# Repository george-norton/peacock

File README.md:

# Peacock

Peacock is an RP2040 powered trackpad running QMK. It features an integrated Microchip MaxTouch sensor IC which is connected to a 7" capacitive sensor. I also designed some little trackpads which you can integrate into your own keyboards, see [Procyon](https://github.com/george-norton/procyon).

The [Ploopy trackpad](https://ploopy.co/trackpad/) is like a more polished Peacock, with a higher resolution sensor. It runs code build from the same QMK/ZMK branches, and is easier to buy.

## Features
- Fully PCBA, this other than switches and encoders, this board is designed to be fully factory assembled.
- Integrated RP2040 controller, no need to a separate controller.
- 7 inch 16:9 capacitive sensor.
- 5 Choc/MX switches and 2 EC11/EC12 encoders.
- A [VIK](https://github.com/sadekbaroudi/vik) connection between the controller and sensor board.

## But how does it work?
The capacitive sensing IC is wired to a grid of diamond shaped electrodes. The diamonds are connected to form rows and columns. The IC scans the matrix by
applying a small voltage to the rows in turn, and then measuring voltage on the columns. Any conductive objects nearby (like your finger) will distrupt the
electrical field and can be detected.

## Sensor capabilities
The mXT336UD-MAU002 sensor IC used in this design is in fact a touchscreen controller rather than a trackpad controller. I have chosen to use a touchscreen
controller as they tend to be designed for much larger sensor areas than touchpad controller. This sensor can:
- Detect 10 concurrent touch events.
- Can support both mutual capacitance and self capacitance measurements.
- Has integrated signal processing capabilities to reduce noise, reject large touches (grip or palms) etc..
- Can be configured as a digitizer, or an array of up to 16 buttons.
- The sensor also supports a passive stylus, although the electrodes in Peacock are larger than the recommended size, so this may not perform well.

## Software support
Currently there are experimental QMK and ZMK branches with Peacock support.

The [QMK multitouch_experiment branch](https://github.com/george-norton/qmk_firmware/tree/multitouch_experiment) exteneds the QMK digitizer feature to implement real trackpad support. On this branch, the MaxTouch driver reports 5 separate finger positions to the host and it detects gestures. You should get all the same gesture support you would expect from a modern trackpad. This branch is a large changeset which will likely take some time to get merged into QMK. There are some [pre-built QMK firmware images in my userspace](https://github.com/george-norton/qmk_userspace/releases/tag/latest).

The [ZMK Maxtouch module](https://github.com/george-norton/maxtouch-zephyr-module) builds against Petes [feat/pointers-move-scroll-ptp](https://github.com/petejohanson/zmk/tree/feat/pointers-move-scroll-ptp) ZMK branch. It is currently missing LED support, and fallback to mouse emulation (so no MacOS support).

## Sensor tuning
The sensor sensitivity may require tuning depending on the type of surface you use on your build. This can be done by adjusting the touch threshold, and
if required the transmit gain. If your sensor is not detecting touches well, reduce the touch threshold. If your sensor is jittery, or is detecting spurious touches increase the touch threshold, or if there is any ungrounded metal by the sensor, move it. Increasing the transmit gain will require a larger touch threshold, but it should enable you to use thicker overlays and it will give you more room to adjust the touch threshold.

The mouse emulation gestures are implemented in software, they rely on various parameters that can be tuned by defining macros.

If you flash the QMK debug firmware, you can use the [Maxtouch debug](https://github.com/george-norton/maxtouch-debug) tool to adjust the sensor tuning in real time and see how it works.

## BOM
To build a Peacock you will need:
- Factory assembled PCBs (from, for example JLCPCB).
- 5 Choc v1 or MX switches.
- 5 keycaps.
- 2 Encoders (ec11/ec12).
- 2 Encoder knobs.
- 1 Type-A 12P 0.5 mm pitch FFC cable (ideally around 5cm long) [aliexpress](https://www.aliexpress.com/item/1005004140412156.html).
- [A 3D printed case](case/) and its mounting fixtures.
- Some sort of nice feeling insulating surface to put over the sensor, for example sticky vinyl wrap or acrylic. Ideally this should not have any air gaps, so FDM printed surfaces should be printed with 100% infill. If the surface is too thin the trackpad will not perform well, multiple layers of vinyl may be required.
- 4 rubber bumpons.

## PCB ordering guide
Use the gerbers files in the releases, most options are not critical although a thicker PCB is probably best so it does not flex too much when you press against the sensor.
I have tested with 1.6mm thickness, lead free HASL from JLCPCB.

The sensor IC is not available from LCSC, you will need to use JLCPCB's global parts sourcing service to order chips from Digikey, the digikey part number is 150-ATMXT336UD-MAU002-ND, expect a lead time of 1-2 weeks. You may also find the flash memory and LED parts go in and out of stock, so it might also be worth preordering those. The LEDs are optional, if the are not available you can always hand solder some at a later time.

You can see the correct part orientation here, when ordering ensure that all parts are correctly rotated:

The v1.0 release has been tested and it works, but there is an issue with the I2C pin allocation. As a result it requires two additional bodge wires, and the encoder switches will not work.

The v1.01 release has the issue fixed, you should order this version.

## Assembly guide

Assembly is simple as the majority of the work is done by the manufacturer. You will need to:

- Remove the edge rails by breaking them off with a pair of pliers, then cut or break the mousebites to separate the two PCBs.

- Test your PCB. Plug it in and hopefully you will see a new mass storage device. Drag and drop a firmware (uf2) file to flash it. If sucessfull, the LEDs should light up.
- Solder 5 MX/Choc switches.
- Solder 2 EC11/EC12 encoders.

- Connect both boards together using the FFC cable, the black parts of the connector can be opened to enable you to insert the cable.

- Use a thread tapping tool to create threads in the case.
- Place the boards into the case.
- Screw it in with 8xM3 6mm screws and optionally 1xM2 6mm screw near the USB port.
- Stick your surface to the sensor area. The surface is critical to the performance of the trackpad, without a surface you will likley get no movement at all. Depending on its thickness, a single piece of vinyl will likely be insufficient for the trackpad to track well, a two or three layers will work much better. I noticed that some battery powered USB hosts require additional surface thickness to track multiple fingers well.

If you build a Peacock, please post a picture in the [show and tell](https://github.com/george-norton/peacock/discussions/categories/show-and-tell).

## Firmware

Peacock support has not yet been merged back to QMK. You can find a branch with pointing device support [here](https://github.com/george-norton/qmk_firmware/tree/peacock) or the multitouch branch [here](https://github.com/george-norton/qmk_firmware/tree/multitouch_experiment) Note, this branch currently does not work with MacOS.

## VIK support

This trackpad is a VIK device, so you should be able to discard the controller portion of the build and wire the trackpad directly to a different VIK enabled controller (such as those sold by fingerpunch and splitkb). You could also replace the controller board with one of your own design.

## VIK certification

Trackpad module

| Category                | Classification          | Response           |
| ----------------------- | ----------------------- | ------------------ |
| FPC connector           | Required                | :heavy_check_mark: |
| Breakout pins           | Recommended             | :heavy_check_mark: |
| Uses: SPI               | Optional                | :x:                |
| SPI used for SPI only   | Strongly recommended    | N/A                |
| Uses: I2C               | Optional                | :heavy_check_mark: |
| I2C used for I2C only   | Strongly Recommended    | :heavy_check_mark: |
| I2C pull ups            | Required                | 3.3k               |
| Uses: RGB               | Optional                | :x:                |
| Uses: Extra GPIO 1      | Optional                | :heavy_check_mark: |
| Uses: Extra GPIO 2      | Optional                | :x:                |
| Standard PCB Size/Mount | Strongly recommended    | :x:                |

Peacock controller

| Category                 | Classification          | Response           |
| -----------------------  | ----------------------- | ------------------ |
| FPC connector            | Required                | :heavy_check_mark: |
| Breakout pins            | Recommended             | :heavy_check_mark: |
| Supplies: SPI            | Required                | :heavy_check_mark: |
| Supplies: I2C            | Required                | :heavy_check_mark: |
| I2C on main PCB          | Discouraged             | :x:                |
| I2C pull ups             | Informative             | N/A                |
| Supplies: RGB            | Required                | :heavy_check_mark: |
| Supplies: Extra GPIO 1   | Required                | Analog/Digital     |
| Supplies: Extra GPIO 2   | Required                | Analog/Digital     |

## Schematic

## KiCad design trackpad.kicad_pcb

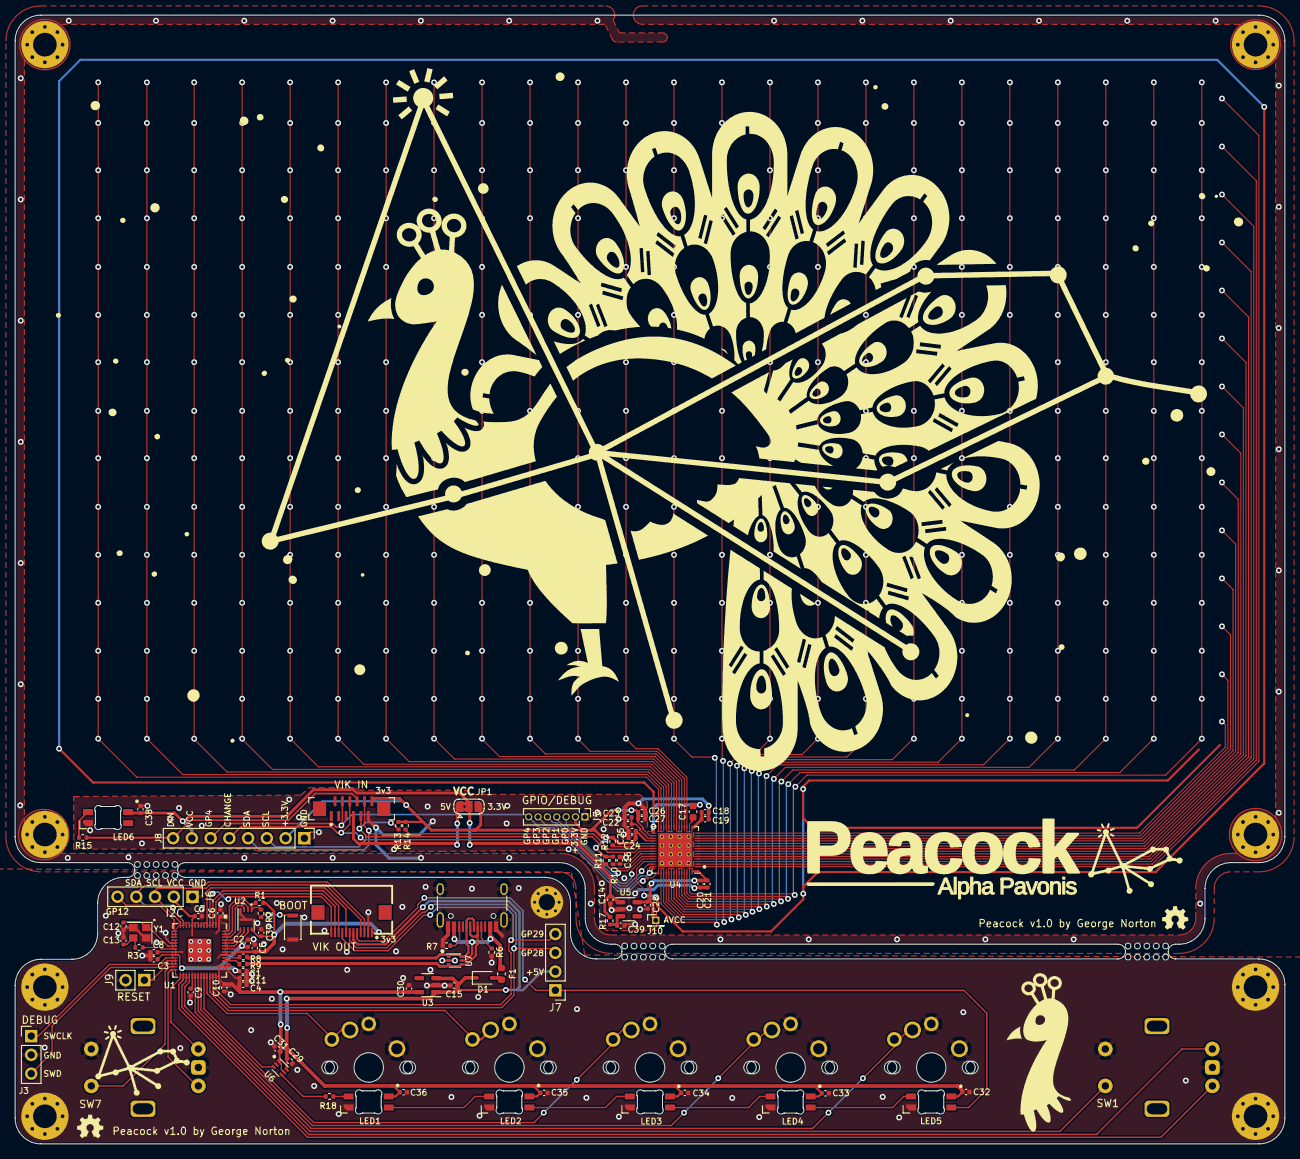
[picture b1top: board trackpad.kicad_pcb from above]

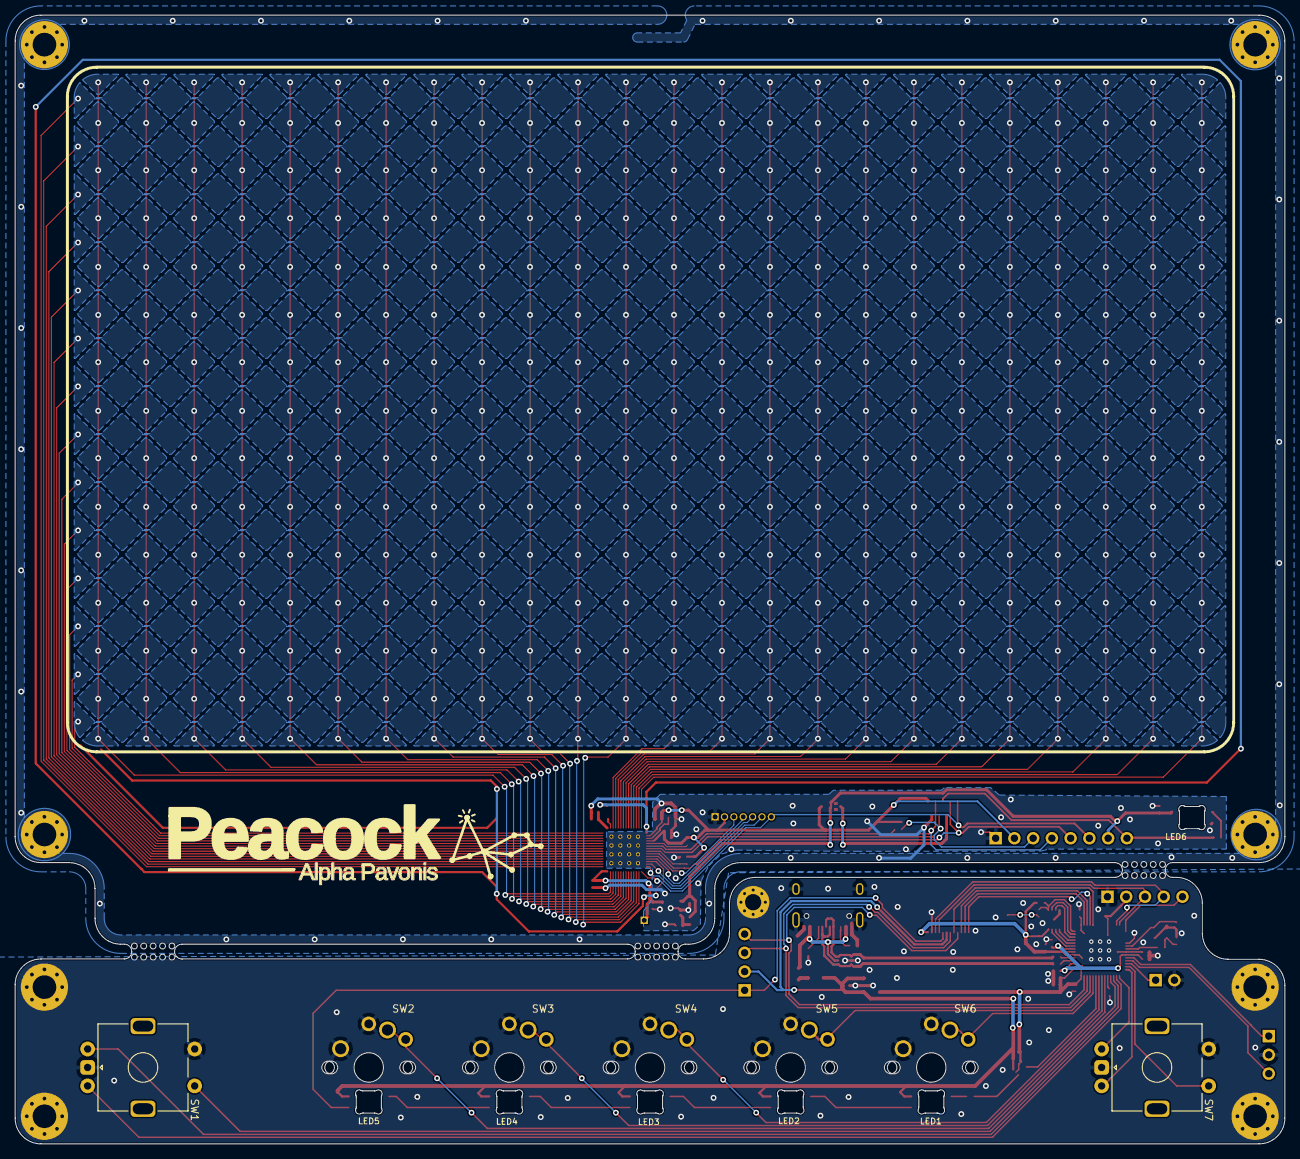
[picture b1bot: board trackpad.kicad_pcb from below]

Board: 2 copper layers, 172.0 x 152.9 mm, 98 parts (7 on the bottom side), 75 nets.

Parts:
C1, C4, C14, C15, C18, C22, C28, C30: 1µ; C_0402_1005Metric
C2, C3, C5, C6, C7, C8, C9, C10, C11, C29, C31, C32, C33, C34, C35, C36, C37, C38: 100n; C_0402_1005Metric
C12, C13: 15p; C_0402_1005Metric
C16, C39: 10nF; C_0402_1005Metric
C17: 2.2nF; C_0603_1608Metric
C19, C21, C23, C25, C27: 22n; C_0402_1005Metric
C20, C24, C26: 2.2µ; C_0402_1005Metric
D1: B5817; D_SOD-323
F1: Polyfuse; Fuse_0603_1608Metric
H1, H2, H3, H4: MountingHole_Pad; MountingHole_3.2mm_M3_Pad_Via
H5, H7, H8, H9: MountingHole; MountingHole_3.2mm_M3_Pad_Via
H6: MountingHole; MountingHole_2.2mm_M2_Pad_Via
J1: USB_C_Receptacle_USB2.0; USB_C_Receptacle_HRO_TYPE-C-31-M-12
J2: vik-keyboard-connector-horizontal
J3: Conn_01x03; PinHeader_1x03_P2.54mm_Vertical
J4: vik-module-connector-vertical
J5: Conn_01x07_Pin; PinHeader_1x07_P1.27mm_Vertical
J6: Conn_01x05_Pin; PinHeader_1x05_P2.54mm_Vertical
J7: Conn_01x04_Pin; PinHeader_1x04_P2.54mm_Vertical
J8: Conn_01x08_Pin; PinHeader_1x08_P2.54mm_Vertical
J9: Conn_01x02_Pin; PinHeader_1x02_P2.54mm_Vertical
J10: Conn_01x01_Pin; PinHeader_1x01_P1.27mm_Vertical
JP1: SolderJumper_3_Open; SolderJumper-3_P1.3mm_Bridged2Bar12_RoundedPad1.0x1.5mm
LED1, LED2, LED3, LED4, LED5, LED6: SK6812-MINI-E; LED_6028R
R1, R11, R12, R17: 10k; R_0402_1005Metric
R2, R3: 1k; R_0402_1005Metric
R6, R7: 5.1k; R_0402_1005Metric
R8, R9: 27; R_0402_1005Metric
R10: 12k; R_0402_1005Metric
R13, R14: 3.3k; R_0402_1005Metric
R15, R18: 330; R_0402_1005Metric
SW1, SW7: RotaryEncoder_Switch; ROT_Alps_EC11E-Switch
SW2, SW3, SW4, SW5, SW6: SW_Push; SW_choc_MxCombo_1u
SW_BOOT1: SW_Push; SW_SPST_CK_KXT3
U1: RP2040; QFN-56-1EP_7x7mm_P0.4mm_EP3.2x3.2mm
U2: W25Q16JVUXIQ; USON-8-1EP_3x2mm_P0.5mm_EP0.25x1.65mm
U3, U5: MIC5504-3.3YM5; SOT-23-5
U4: mXT336UD-MAU002; QFN-56_EP_6x6_Pitch0.35mm
U6: SN74LVC1T45DRL; SN74LVC1T45DRLR
U7: USBLC6-2P6; SOT-666
Y1: Crystal_GND24; Crystal_SMD_2520-4Pin_2.5x2.0mm

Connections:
+1V1: C1.1, C2.1, C3.1, U1.23 (DVDD), U1.45 (VREG_VOUT), U1.50 (DVDD)
+3.3V: C4.1, C5.1, C6.1, C7.1, C8.1, C9.1, C10.1, C11.1, C30.1, C31.1, C37.2, J2.1 (3V3), J6.2, R1.1, U1.1 (IOVDD), U1.10 (IOVDD), U1.22 (IOVDD), U1.33 (IOVDD), U1.42 (IOVDD), U1.43 (ADC_AVDD), U1.44 (VREG_IN), U1.48 (USB_VDD), U1.49 (IOVDD), U2.8 (VCC), U3.5 (VOUT), U6.1 (VCCA), U6.5 (DIR)
+3.3VA: C20.2, C21.2, C28.1, J10.1, U4.56 (AVDD), U5.5 (VOUT)
+3V3: C24.2, C25.2, C26.2, C27.2, J4.12 (3V3), J5.2, J8.2, JP1.3 (B), R10.1, R11.1, R12.1, R13.1, R14.1, U4.30 (VDD), U4.32 (VDDIO)
+5V: C15.1, C29.1, C32.1, C33.1, C34.1, C35.1, C36.1, D1.1 (K), J2.6 (5V), J7.2, LED1.1 (VDD), LED2.1 (VDD), LED3.1 (VDD), LED4.1 (VDD), LED5.1 (VDD), U3.1 (VIN), U3.3 (EN), U6.6 (VCCB)
/Macropad/D+: J1.A6 (D+), J1.B6 (D+), R8.2, U7.1 (I/O1), U7.6 (I/O1)
/Macropad/D-: J1.A7 (D-), J1.B7 (D-), R9.2, U7.3 (I/O2), U7.4 (I/O2)
/Macropad/ENC1_A: SW1.A, U1.31 (GPIO20)
/Macropad/ENC1_B: SW1.B, U1.30 (GPIO19)
/Macropad/ENC2_A: SW7.A, U1.29 (GPIO18)
/Macropad/ENC2_B: SW7.B, U1.28 (GPIO17)
/Macropad/GP12: J6.5, U1.15 (GPIO12)
/Macropad/GPIO_AD1: J2.7 (GPIO_AD1), J7.3, U1.40 (GPIO28_ADC2)
/Macropad/GPIO_AD2: J2.9 (GPIO_AD2), J7.4, U1.41 (GPIO29_ADC3)
/Macropad/LED_3.3V: U1.37 (GPIO25), U6.3 (A)
/Macropad/MISO: J2.11 (MISO), U1.2 (GPIO0)
/Macropad/MOSI: J2.8 (MOSI), U1.5 (GPIO3)
/Macropad/RUN: J9.1, U1.26 (RUN)
/Macropad/SCL: J2.4 (SCL), J6.3, U1.14 (GPIO11)
/Macropad/SCLK: J2.12 (SCLK), U1.4 (GPIO2)
/Macropad/SDA: J2.3 (SDA), J6.4, U1.13 (GPIO10)
/Macropad/SPI_CS: J2.10 (SPI_CS), U1.3 (GPIO1)
/Macropad/SW1: SW1.S1, U1.32 (GPIO21)
/Macropad/SW2: SW2.2, U1.34 (GPIO22)
/Macropad/SW3: SW3.2, U1.35 (GPIO23)
/Macropad/SW4: SW4.2, U1.36 (GPIO24)
/Macropad/SW5: SW5.2, U1.39 (GPIO27_ADC1)
/Macropad/SW6: SW6.2, U1.38 (GPIO26_ADC0)
/Macropad/SW7: SW7.S1, U1.27 (GPIO16)
/Macropad/VIK_RGB: J2.5 (RGB_LED_OUT), J7.1, LED5.2 (DOUT)
/Sensor/CHANGE: J4.6 (GPIO_AD1), J8.5, R11.2, U4.37 (CHG)
/Sensor/GPIO0: J5.3, U4.38 (GPIO0)
/Sensor/GPIO1: J5.4, U4.39 (GPIO1)
/Sensor/GPIO2: J5.5, U4.41 (GPIO2)
/Sensor/GPIO3: J5.6, U4.42 (GPIO3)
/Sensor/GPIO4: J4.4 (GPIO_AD2), J5.7, J8.6, U4.43 (GPIO4)
/Sensor/RESET: C16.1, R10.2, U4.36 (RESET)
/Sensor/SCL: J4.9 (SCL), J8.3, R13.2, U4.35 (SCL)
/Sensor/SDA: J4.10 (SDA), J8.4, R14.2, U4.34 (SDA)
/Sensor/VIK_5V: J4.7 (5V), JP1.1 (A)
/Sensor/VIK_RGB: J4.8 (RGB_LED_IN), J8.8, R15.2
GND: C1.2, C2.2, C3.2, C4.2, C5.2, C6.2, C7.2, C8.2, C9.2, C10.2, C11.2, C12.2, C13.2, C15.2, C29.2, C30.2, C31.2, C32.2, C33.2, C34.2, C35.2, C36.2, C37.1, H5.1, H6.1, H7.1, H8.1, H9.1, J1.A1 (GND), J1.A12 (GND), J1.B1 (GND), J1.B12 (GND), J1.S1 (SHIELD), J2.2 (GND), J3.2, J6.1, J9.2, LED1.4 (VSS), LED2.4 (VSS), LED3.4 (VSS), LED4.4 (VSS), LED5.4 (VSS), R6.2, R7.2, SW1.C, SW1.S2, SW2.1, SW3.1, SW4.1, SW5.1, SW6.1, SW7.C, SW7.S2, SW_BOOT1.1, U1.19 (TESTEN), U1.57 (GND), U2.4 (GND), U2.9 (EP), U3.2 (GND), U6.2 (GND), U7.2 (GND), Y1.2, Y1.4
GND2: C14.2, C16.2, C18.2, C19.2, C20.1, C21.1, C22.1, C23.1, C24.1, C25.1, C26.1, C27.1, C28.2, C38.2, C39.2, H1.1, H2.1, H3.1, H4.1, J4.11 (GND), J5.1, J8.1, LED6.4 (VSS), U4.57 (GND), U5.2 (GND)
unnamed: C13.1, R3.2, Y1.3
unnamed: D1.2 (A), F1.1
unnamed: J1.A5 (CC1), R6.1
unnamed: J1.B5 (CC2), R7.1
unnamed: J3.1, U1.24 (SWCLK)
unnamed: J3.3, U1.25 (SWD)
unnamed: LED1.3 (DIN), R18.1
unnamed: LED1.2 (DOUT), LED2.3 (DIN)
unnamed: LED2.2 (DOUT), LED3.3 (DIN)
unnamed: LED3.2 (DOUT), LED4.3 (DIN)
unnamed: LED4.2 (DOUT), LED5.3 (DIN)
unnamed: LED6.3 (DIN), R15.1
unnamed: R2.1, SW_BOOT1.2
unnamed: U1.52 (QSPI_SCLK), U2.6 (CLK)
unnamed: U1.53 (QSPI_SD0), U2.5 (DI(IO0))
unnamed: U1.55 (QSPI_SD1), U2.2 (DO(IO1))
unnamed: U1.54 (QSPI_SD2), U2.3 (IO2)
unnamed: U1.51 (QSPI_SD3), U2.7 (IO3)
unnamed: R1.2, R2.2, U1.56 (QSPI_SS), U2.1 (~CS)
unnamed: R9.1, U1.46 (USB_DM)
unnamed: R8.1, U1.47 (USB_DP)
unnamed: C12.1, U1.20 (XIN), Y1.1
unnamed: R3.1, U1.21 (XOUT)
unnamed: C17.2, U4.29 (EXCAP0)
unnamed: C17.1, U4.16 (EXCAP1)
unnamed: R12.2, U4.33 (TEST)
unnamed: C22.2, C23.2, U4.31 (VDDCORE)
unnamed: C18.1, C19.1, U4.15 (XVDD)
unnamed: C39.1, R17.2, U5.3 (EN)
unnamed: R18.2, U6.4 (B)
VBUS: F1.2, J1.A4 (VBUS), J1.A9 (VBUS), J1.B4 (VBUS), J1.B9 (VBUS), U7.5 (VBUS)
VCC: C14.1, C38.1, J8.7, JP1.2 (C), LED6.1 (VDD), R17.1, U5.1 (VIN)

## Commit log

2023-12-15 Initial commit of 'peacock'
2023-12-15 Cleanup libraries
2023-12-20 Switch LDO for a cheaper part.
2023-12-22 Move USB port closer to the edge, Additional silkscreen, Add reset header, shrink LDO caps, swap QSPI flash.
2024-01-02 Re-route to avoid crossing the USB data lines. Reduced keys to 5 to avoid having to route a long trace around the crystal, swaped key footprint from choc hotswap to mx/choc combined soldered.
2024-01-03 Minor cleanups. Made the mounting hole distances round numbers, cleaned up a few traces.
2024-01-05 Modify EC11 footprint to allow SMT parts. Add resistors to the LED data lines.
2024-01-05 Fix DRC issue and add VCC warning.
2024-01-05 Tweak fills.
2024-01-11 Minor tweaks
2024-01-11 Add missing paste on max touch epad.
2024-01-12 Use encroached vias. Update footprints
2024-01-12 Cleanup
2024-01-12 Modifications before initial order.
2024-01-29 First check-in of the documentation. Missing build instructions.
2024-01-29 Use less offensive colours on the sensor image.
2024-01-29 Simplify sensor diagram.
2024-02-05 initial case files for low version
2024-02-05 add overlay template
2024-02-05 Delete case/trackpad-B_Silkscreen.dxf
    accidental addition.
2024-02-08 correct svg and dxf files for scaling
2024-02-08 update case/readme to reflect all hardware
2024-02-08 further SVG adjustments after test cutting
2024-02-08 add v5 case- improved bolt tolerances
2024-02-08 remove v4 files
2024-02-08 update gitignore for macos fluff
2024-02-08 I2C pins were incorrect.
2024-02-08 Fixes for minor issues in the v1.0 PCB.
2024-02-08 Fixup LSCS part number miss-match between PCB and schematic.
2024-02-09 Show part orientation and link to case
2024-02-09 Expand software support and assembly guide.
2024-02-09 Spelling.
2024-02-09 v5 case correction
2024-02-14 Expand build guide.
2024-02-15 Cleanup readme.
2024-02-22 Extra notes on the surface.
2024-03-21 Fix minor issues reported by JLC, and replace parts which are often out of stock.
2024-03-22 Swap the VIK connector part for the default, the new part has pin 1 labelled differently
2024-03-22 Update the submodules. New VIK vertical silkscreen and LED silkscreen, maybe it will prevent JLC querying the orientation
2024-11-30 Add schematics
2025-01-28 Add Peacock case with 5 deg tilt
2025-02-02 Add image of the new case type
2025-02-02 Fix image link
2025-02-03 Readme updates.
